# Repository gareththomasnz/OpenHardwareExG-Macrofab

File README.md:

Microfab prototype files

3x Boards for OpenHardwareEXG EEG 8 channel device

ADS1299 Board

Analog Board

Digital Board

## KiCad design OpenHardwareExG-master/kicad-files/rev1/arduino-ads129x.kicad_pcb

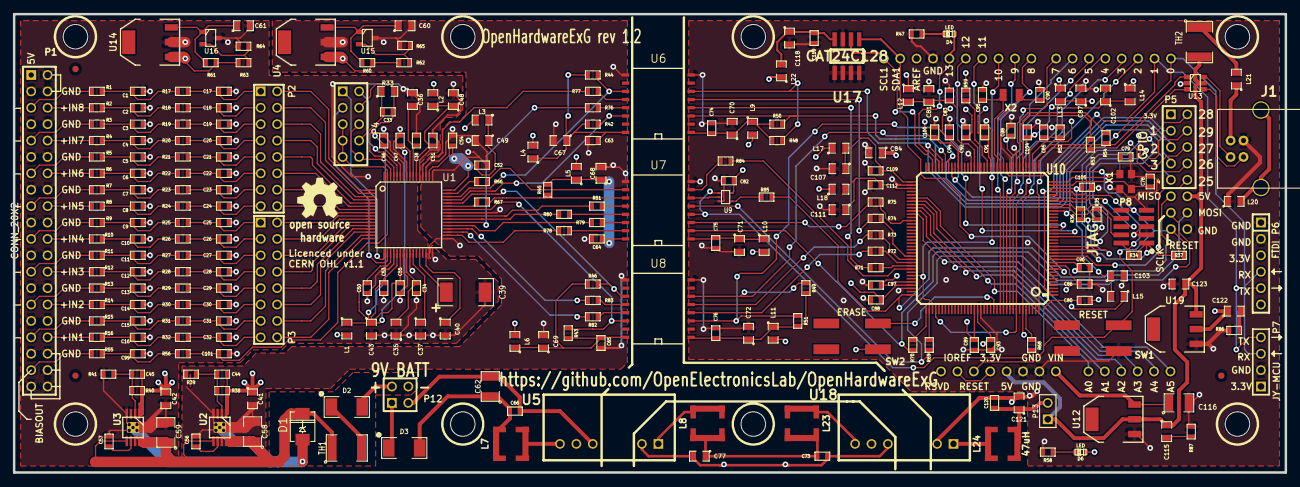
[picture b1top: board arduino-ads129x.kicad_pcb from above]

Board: 4 copper layers, 197.0 x 71.0 mm, 277 parts (0 on the bottom side), 221 nets.

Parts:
C1, C2, C3, C4, C5, C6, C7, C8, C9, C10, C11, C12, C13, C14, C15, C16, C17, C18, C19, C20, C21, C22, C23, C24, C25, C26, C27, C28, C29, C30, C31, C32, C99, C101: 270pF; SM0603
C33: 1.5nF; SM0603
C34, C38, C44, C45, C46, C47, C50, C51, C52, C53, C54, C55, C56, C57, C63, C64, C65, C66, C73, C74, C75, C76, C80, C82, C83, C86, C88, C89, C91, C92, C93, C94, C96, C97, C98, C100, C104, C105, C109, C112, C119, C120: 100nF; SM0603
C35, C36, C37, C40, C41, C42, C43, C48, C49, C60, C61, C67, C68, C69, C70, C71, C72, C77, C81, C84, C87, C102, C103, C107, C111, C115, C118, C121, C122, C123: 10uF; SM0805
C39: 100uF; SM2512
C58, C59, C62, C116: 10uF; SM1210
C78, C79, C85, C90, C95: 22pF; SM0603
D1: BZG03C27TR; DO214
D2, D3: CMS06; SM2010
D4, D6: LED; LED-0603
Hole_M3, Hole_M3#2, Hole_M3#3, Hole_M3#4, Hole_M3#5, Hole_M3#6, Hole_M3#7, Hole_M3#8: VAL**; Hole_M3
J1: USB_1; USB_B
L1, L2, L3, L4, L5, L6, L9, L10, L11, L12, L13, L14, L15, L17, L18, L20, L21, L22: MH2029-221Y; SM0805
L7, L8, L23, L24: 47uH; SRR4028
P1: CONN_20X2; PIN_ARRAY_20X2
P2, P3: CONN_8X2; pin_array_8x2
P4, P5: CONN_5X2; PIN_ARRAY_5x2
P6: FTDI; PIN_ARRAY-6X1
P7: JY-MCU; PIN_ARRAY_4x1
P8: JTAG; SMT_PIN_2x5
P11: ARDUINO_SHIELD; arduino_shield
P12: CONN_2; PIN_ARRAY_2X2
P13: CONN_2; PIN_ARRAY_2X1
R1, R2, R3, R4, R5, R6, R7, R8, R9, R10, R11, R12, R13, R14, R15, R16, R17, R18, R19, R20, R21, R22, R23, R24, R25, R26, R27, R28, R29, R30, R31, R32, R55, R56: 2.61k; SM0603
R33: 1M; SM0805
R34, R35, R36, R37, R59: 100k; SM0603
R38: 68.1k; SM0603
R39, R41: 39.2k; SM0603
R40: 124k; SM0603
R42, R43, R44, R45, R46, R48, R49, R50, R51: 10k; SM0603
R47: 1k; SM0603
R52: 6.8k; SM0603
R53, R54: 39; SM0603
R58: 560; SM0603
R60, R61: 68; SM0603
R62, R63: 10.0k; SM0603
R64: 8.45k; SM0603
R65: 19.6k; SM0603
R66, R67, R68, R69, R70, R71, R72, R73, R74, R75, R76, R77, R78, R79, R80, R81, R82, R83, R84, R85: 47; SM0603
R86, R87: 30m; SM0603
SW1, SW2: SW_PUSH; smt-tactile-button
TH1: PTS181260V014; SM1812
TH2: MINIASMDC050F-2; SM1812
U1: ADS1299; TQFP_64
U2, U3: TPS7A49XX; MSOP8_PowerPad
U4, U14: BT1308W-600D; SOT223
U5: R05P209/R6; SIP7_ISOLATOR
U6, U8: SI8606; SO16W
U7: SI8662; SO16W
U9: 74AUP1G125GW; SOT353
U10: SAM3X8E; TQFP144
U12: NCP1117ST50T3G; SOT223
U13: USBLC6; SOT23_6
U15, U16: TL431BIDBZR; SOT23
U17: CAT24C128; SOIC8
U18: R05P205/R6; SIP7_ISOLATOR
U19: NCP1117LPST33T3G; SOT223
X1: ECS-120-20-33-CKM-TR; smt-crystal-3.2x2.5
X2: ABS07-32.768KHZ-T; ABS07
fiducial_mark: VAL**; fiducial_mark
fiducial_mark#2, fiducial_mark#3: VAL**; fiducial_mark

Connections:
+3.3V: C82.1, C122.1, D6.1, L9.2, L10.2, L11.2, L12.1, L13.1, L14.1, L17.1, L18.1, L22.1, P5.1, P6.3, P7.1, P8.1, P11.91, P11.93, R34.1, R35.1, R36.1, R37.1, R59.2, SW2.1, U9.5, U19.2
+3.3VADC: C49.1, C52.1, C54.1, L3.1, U1.48, U1.50
+5V: C115.1, C123.1, P11.88, P11.94, P13.1, TH2.2, U12.2, U13.5, U19.3
+5VA: C43.1, C46.1, C47.1, C50.1, C53.1, C55.1, L1.1, U1.19, U1.21, U1.22, U1.56, U1.59
/3.3V_ISO: C41.1, C44.1, L3.2, L4.2, L5.2, L6.2, R38.1, R60.1, R62.1, U2.1, U4.1
/5V_ISO: C42.1, C45.1, L1.2, L2.2, P1.1, R40.1, R61.1, R63.1, U3.1, U14.1
/5V_in_prefilter: C120.1, C121.1, L24.1, P13.2
/9V_ISO: C58.1, C59.1, D1.2, TH1.1, U2.5, U2.8, U3.5, U3.8
/9V_iso_postfilter: C62.1, C66.1, D3.1, L7.2
/ADS129x_CLK: R75.2, U7.3
/ADS129x_CLKSEL: R74.2, U6.5
/ADS129x_CLKSEL_ISO: R77.1, U1.52
/ADS129x_CLK_ISO: R79.1, U1.37
/ADS129x_GPIO1: P5.3, R51.2, U8.3, U10.64
/ADS129x_GPIO1_ISO: R43.2, U1.42, U8.14
/ADS129x_GPIO2: P5.5, R49.2, U8.6, U10.65
/ADS129x_GPIO2_ISO: R46.2, U1.44, U8.11
/ADS129x_GPIO3: P5.7, R50.2, U6.3, U10.66
/ADS129x_GPIO3_ISO: R42.2, U1.45, U6.14
/ADS129x_GPIO4: P5.9, R48.2, U6.6, U10.67
/ADS129x_GPIO4_ISO: R44.2, U1.46, U6.11
/ADS129x_MISO: U7.6, U9.2
/ADS129x_MISO_ISO: R45.2, R67.2, U7.11
/ADS129x_MOSI_ISO: R78.1, U1.34
/ADS129x_SCLK_ISO: R81.1, U1.40
/ADS129x_START: R71.2, U6.4
/ADS129x_START_ISO: R76.1, U1.38
/ADS129x_~CS~: R68.2, U7.4, U9.1
/ADS129x_~CS~_ISO: R80.1, U1.39
/ADS129x_~DRDY~: R84.2, U10.100
/ADS129x_~DRDY~_ISO: R66.2, U7.10
/ADS129x_~PWDN~: R72.2, U8.4
/ADS129x_~PWDN~_ISO: R82.1, U1.35
/ADS129x_~RESET~: R73.2, U8.5
/ADS129x_~RESET~_ISO: R83.1, U1.36
/ADVREF: C111.1, C112.1, L18.2, U10.75
/AVDD1: C48.1, C51.1, L2.1, U1.54
/BIASOUT: C101.1, P4.5, P4.7, P4.9, R56.2, U1.63
/BIASOUT_FILT: P1.37, R55.1
/IN1N: P1.33, R15.1
/IN1P: P1.34, R16.1
/IN2N: P1.29, R13.1
/IN2P: P1.30, R14.1
/IN3N: P1.25, R11.1
/IN3P: P1.26, R12.1
/IN4N: P1.21, R9.1
/IN4P: P1.22, R10.1
/IN5N: P1.17, R7.1
/IN5P: P1.18, R8.1
/IN6N: P1.13, R5.1
/IN6P: P1.14, R6.1
/IN7N: P1.9, R3.1
/IN7P: P1.10, R4.1
/IN8N: P1.5, R1.1
/IN8P: P1.6, R2.1
/JTAG_RESET: C80.1, P8.10, P11.89, P11.92, R37.2, SW1.2, U10.47
/JTAG_TCK: P8.4, R35.2, U10.28
/JTAG_TDI: P8.8, R36.2, U10.29
/JTAG_TDO: P8.6, U10.30
/JTAG_TMS: P8.2, R34.2, U10.31
/LED_LATCH_CLK: P5.2, U10.16
/LED_OUTPUT_ENABLE_INPUT: P5.4, U10.19
/LED_SERIAL: P5.10, U10.13
/LED_SHIFT_REG_CLEAR: P5.6, U10.15
/LED_SHIFT_REG_CLK: P5.8, U10.14
/PA4_A5: P11.59, U10.83
/PA6_A4: P11.58, U10.82
/PA8_RX: P6.4, P7.3, P11.0, U10.27
/PA9_TX: P6.5, P7.4, P11.1, U10.2
/PA16_A0: P11.54, U10.78
/PA17_SDA1: P11.70, U10.9, U17.5
/PA18_SCL1: P11.71, U10.70, U17.6
/PA22_A3: P11.57, U10.81
/PA23_A2: P11.56, U10.80
/PA24_A1: P11.55, U10.79
/PA25_MISO: P11.74, R85.2, U10.108
/PA26_MOSI: P11.75, R70.2, U7.2
/PA27_SCLK: P11.76, R69.2, U7.5
/PA28_SS0: P11.10, U10.102, U10.111
/PA29_SS1: P11.4, U10.112, U10.137
/PB25_PWM2: P11.2, U10.144
/PB27_PWM13: D4.1, P11.13, U10.68
/PC20_ERASE: SW2.2, U10.130
/PC21_PWM9: P11.9, U10.132
/PC22_PWM8: P11.8, U10.133
/PC23_PWM7: P11.7, U10.134
/PC24_PWM6: P11.6, U10.135
/PC25_PWM5: P11.5, U10.136
/PC28_PWM3: P11.3, U10.139
/PD7_PWM11: P11.11, U10.20
/PD8_PWM12: P11.12, U10.21
/SRB1: P4.1, U1.17
/SRB2: P4.3, U1.18
/USB_DATA_M: R54.2, U10.38, U13.1
/USB_DATA_P: R53.2, U10.37, U13.3
/VDDANA: C107.1, C109.1, L17.2, U10.73
/VDDBU: C80.2, C87.1, C88.1, C91.1, C93.1, C96.1, C100.1, L13.2, U10.11, U10.39, U10.52, U10.62, U10.105, U10.125
/VDDCORE: C84.1, C86.1, C89.1, C92.1, C94.1, C97.1, C98.1, L15.1, U10.10, U10.45, U10.56, U10.61, U10.104, U10.124
/VDDIN: C81.1, C83.1, L12.2, U10.57
/VDDPLL: C103.1, C105.1, L15.2, U10.34
/VDDUTMI: C102.1, C104.1, L14.2, U10.41
/V_IN: C116.1, P11.97, U12.3
AGND: C1.2, C2.2, C3.2, C4.2, C5.2, C6.2, C7.2, C8.2, C9.2, C10.2, C11.2, C12.2, C13.2, C14.2, C15.2, C16.2, C17.2, C18.2, C19.2, C20.2, C21.2, C22.2, C23.2, C24.2, C25.2, C26.2, C27.2, C28.2, C29.2, C30.2, C31.2, C32.2, C34.1, C35.1, C36.1, C37.2, C38.1, C39.2, C40.2, C41.2, C42.2, C43.2, C46.2, C47.2, C48.2, C49.2, C50.2, C51.2, C52.2, C53.2, C54.2, C55.2, C56.2, C57.2, C58.2, C59.2, C60.2, C61.2, C63.2, C64.2, C65.2, C67.2, C68.2, C69.2, C99.2, C101.2, D1.1, P1.2, P1.3, P1.4, P1.7, P1.8, P1.11, P1.12, P1.15, P1.16, P1.19, P1.20, P1.23, P1.24, P1.27, P1.28, P1.31, P1.32, P1.35, P1.36, P1.38, P1.39, P1.40, P12.4, R39.2, R41.2, R64.2, R65.2, U1.20, U1.23, U1.25, U1.31, U1.32, U1.33, U1.41, U1.49, U1.51, U1.53, U1.57, U1.58, U2.4, U2.9, U3.4, U3.9, U4.2, U6.9, U7.9, U8.9, U14.2, U15.3, U16.3
GND: C70.2, C71.2, C72.2, C74.2, C75.2, C76.2, C78.2, C79.2, C81.2, C82.2, C83.2, C84.2, C85.2, C86.2, C87.2, C88.2, C89.2, C90.2, C91.2, C92.2, C93.2, C94.2, C95.2, C96.2, C97.2, C98.2, C100.2, C102.2, C103.2, C104.2, C105.2, C107.2, C109.2, C111.2, C112.2, C116.2, C118.2, C119.2, C120.2, C121.2, C123.2, J1.4, L20.1, P6.1, P6.2, P7.2, P8.3, P8.5, P8.9, P11.87, P11.95, P11.96, P11.99, R47.2, R52.2, R58.2, R86.1, R87.1, SW1.1, U6.8, U7.8, U8.8, U9.3, U10.12, U10.33, U10.44, U10.46, U10.51, U10.58, U10.74, U10.106, U10.126, U12.1, U13.2, U17.1, U17.2, U17.3, U17.4, U17.7, U18.2, U19.1, X1.2, X1.4
unnamed: C72.1, C76.1, L11.1, R49.1, R51.1, U8.1
unnamed: C64.1, C68.1, L5.1, R45.1, U7.16
unnamed: C71.1, C75.1, L10.1, U7.1
unnamed: C70.1, C74.1, L9.1, R48.1, R50.1, U6.1
unnamed: C65.1, C69.1, L6.1, R43.1, R46.1, U8.16
unnamed: C56.1, U2.6
unnamed: C57.1, U3.6
unnamed: C45.2, R40.2, R41.1, U3.2
unnamed: R63.2, R64.1, U16.2
unnamed: C60.1, R60.2, U4.3, U15.1
unnamed: C118.1, C119.1, L22.2, U17.8
unnamed: R77.2, U6.12
unnamed: R76.2, U6.13
unnamed: L24.2, U18.1
unnamed: P4.6, P4.10, U1.62
unnamed: P4.2, U1.60
unnamed: R62.2, R65.1, U15.2
unnamed: C79.1, U10.36, X1.3
unnamed: D3.2, P12.1
unnamed: C63.1, C67.1, L4.1, R42.1, R44.1, U6.16
unnamed: D4.2, R47.1
unnamed: C9.1, R9.2, R25.1
unnamed: C25.1, P3.1, R25.2
unnamed: C24.1, P2.15, R24.2
unnamed: C8.1, R8.2, R24.1
unnamed: C31.1, P3.13, R31.2
unnamed: C15.1, R15.2, R31.1
unnamed: C33.1, P4.8, R33.1
unnamed: C28.1, P3.7, R28.2
unnamed: C12.1, R12.2, R28.1
unnamed: P2.14, U1.7
unnamed: P2.16, U1.8
unnamed: C40.1, U1.30
unnamed: P2.2, U1.1
unnamed: C30.1, P3.11, R30.2
unnamed: P2.4, U1.2
unnamed: P2.6, U1.3
unnamed: C20.1, P2.7, R20.2
unnamed: P2.8, U1.4
unnamed: P2.10, U1.5
unnamed: P2.12, U1.6
unnamed: C36.2, C38.2, U1.55
unnamed: P3.16, U1.16
unnamed: C37.1, U1.26
unnamed: R66.1, U1.47
unnamed: R67.1, U1.43
unnamed: P3.8, U1.12
unnamed: P3.10, U1.13
unnamed: P3.12, U1.14
unnamed: C34.2, C35.2, U1.24
unnamed: P3.14, U1.15
unnamed: C18.1, P2.3, R18.2
unnamed: C2.1, R2.2, R18.1
unnamed: C21.1, P2.9, R21.2
unnamed: C5.1, R5.2, R21.1
unnamed: P3.2, U1.9
unnamed: C26.1, P3.3, R26.2
unnamed: P3.4, U1.10
unnamed: P3.6, U1.11
unnamed: C3.1, R3.2, R19.1
unnamed: J1.5, J1.6
unnamed: L7.1, U5.7
unnamed: C73.1, C77.1, L8.1, L23.2
unnamed: C73.2, C77.2, U5.2, U18.5
unnamed: D2.1, P12.2
unnamed: L21.2, TH2.1
unnamed: C85.1, R52.1, U10.40
unnamed: D2.2, TH1.2
unnamed: C90.1, U10.48, X2.1
unnamed: D6.2, R58.1
unnamed: R73.1, U10.97
unnamed: R72.1, U10.98
unnamed: C95.1, U10.49, X2.2
unnamed: C78.1, U10.35, X1.1
unnamed: R75.1, U10.85
unnamed: R74.1, U10.96
unnamed: R71.1, U10.99
unnamed: R69.1, U10.110
unnamed: R68.1, U10.140
unnamed: R54.1, U10.43
unnamed: R59.1, U10.53
unnamed: R53.1, U10.42
unnamed: R83.2, U8.12
unnamed: C39.1, U1.28
unnamed: C4.1, R4.2, R20.1
unnamed: C10.1, R10.2, R26.1
unnamed: C14.1, R14.2, R30.1
unnamed: C27.1, P3.5, R27.2
unnamed: C29.1, P3.9, R29.2
unnamed: C13.1, R13.2, R29.1
unnamed: C11.1, R11.2, R27.1
unnamed: C17.1, P2.1, R17.2
unnamed: C1.1, R1.2, R17.1
unnamed: C19.1, P2.5, R19.2
unnamed: C22.1, P2.11, R22.2
unnamed: C6.1, R6.2, R22.1
unnamed: C32.1, P3.15, R32.2
unnamed: C16.1, R16.2, R32.1
unnamed: C23.1, P2.13, R23.2
unnamed: C7.1, R7.2, R23.1
unnamed: C99.1, R55.2, R56.1
unnamed: C115.2, R87.2
unnamed: C61.1, R61.2, U14.3, U16.1
unnamed: C44.2, R38.2, R39.1, U2.2
unnamed: R85.1, U9.4
unnamed: R84.1, U7.7
unnamed: R81.2, U7.12
unnamed: R80.2, U7.13
unnamed: R78.2, U7.15
unnamed: R79.2, U7.14
unnamed: R82.2, U8.13
unnamed: C122.2, R86.2
unnamed: L23.1, U18.7
unnamed: R70.1, U10.109
unnamed: C33.2, P4.4, R33.2, U1.61
unnamed: L8.2, U5.1
unnamed: C62.2, C66.2, P12.3, U5.5

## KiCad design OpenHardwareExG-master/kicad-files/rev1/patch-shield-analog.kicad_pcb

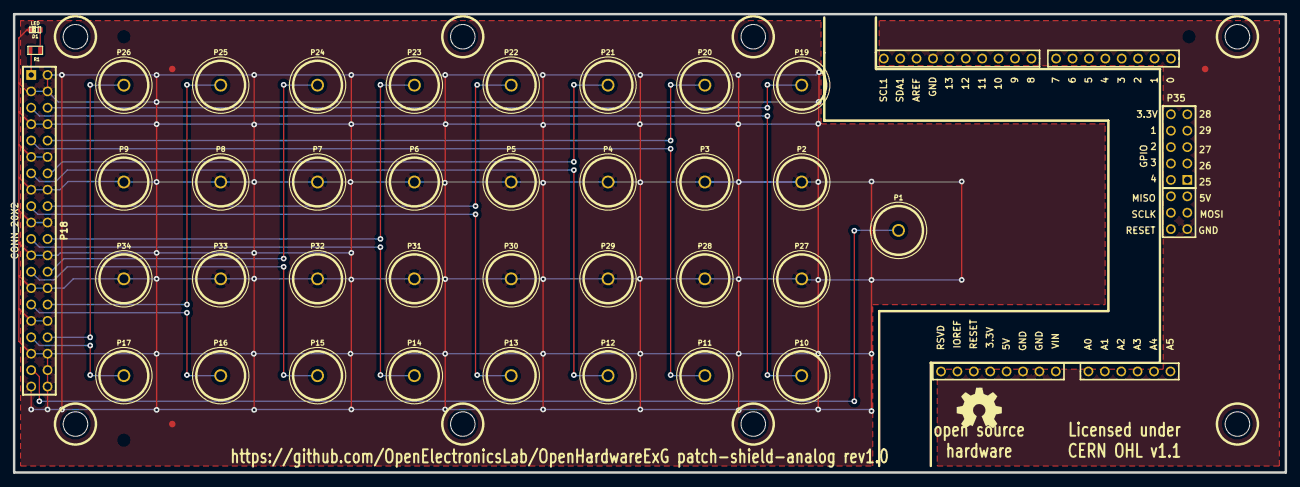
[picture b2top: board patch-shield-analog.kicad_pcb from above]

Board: 2 copper layers, 197.0 x 71.0 mm, 49 parts (0 on the bottom side), 21 nets.

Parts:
D1: LED; LED-0603
Hole_M3, Hole_M3#2, Hole_M3#3, Hole_M3#4, Hole_M3#5, Hole_M3#6, Hole_M3#7, Hole_M3#8: VAL**; Hole_M3
P1, P2, P3, P4, P5, P6, P7, P8, P9, P10, P11, P12, P13, P14, P15, P16, P17, P19, P20, P21, P22, P23, P24, P25, P26, P27, P28, P29, P30, P31, P32, P33, P34: CONN_1; Touchproof-socket
P18: CONN_20X2; PIN_ARRAY_20X2
P35: CONN_5X2; PIN_ARRAY_5x2
P36: ARDUINO_SHIELD; arduino_shield
R1: 1k; SM0603
fiducial_mark: VAL**; fiducial_mark
fiducial_mark#2, fiducial_mark#3: VAL**; fiducial_mark

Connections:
+5VA: P18.1, R1.1
/BIASOUT: P1.1, P18.37
/IN1N: P17.1, P18.33
/IN1P: P18.34, P26.1
/IN2N: P16.1, P18.29
/IN2P: P18.30, P25.1
/IN3N: P15.1, P18.25
/IN3P: P18.26, P24.1
/IN4N: P14.1, P18.21
/IN4P: P18.22, P23.1
/IN5N: P13.1, P18.17
/IN5P: P18.18, P22.1
/IN6N: P12.1, P18.13
/IN6P: P18.14, P21.1
/IN7N: P11.1, P18.9
/IN7P: P18.10, P20.1
/IN8N: P10.1, P18.5
/IN8P: P18.6, P19.1
AGND: D1.2, P2.1, P3.1, P4.1, P5.1, P6.1, P7.1, P8.1, P9.1, P18.2, P18.3, P18.4, P18.7, P18.8, P18.11, P18.12, P18.15, P18.16, P18.19, P18.20, P18.23, P18.24, P18.27, P18.28, P18.31, P18.32, P18.35, P18.36, P18.38, P18.39, P18.40, P27.1, P28.1, P29.1, P30.1, P31.1, P32.1, P33.1, P34.1
DGND: P36.87, P36.95, P36.96, P36.99
unnamed: D1.1, R1.2

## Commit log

2018-02-15 First commit Message
2018-02-15 Second commit Message

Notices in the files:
OpenHardwareExG-master/kicad-files/rev1/arduino-ads129x.kicad_pcb:
Licenced under
CERN OHL v1.1
OpenHardwareExG-master/kicad-files/rev1/patch-shield-analog.kicad_pcb:
Licensed under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
